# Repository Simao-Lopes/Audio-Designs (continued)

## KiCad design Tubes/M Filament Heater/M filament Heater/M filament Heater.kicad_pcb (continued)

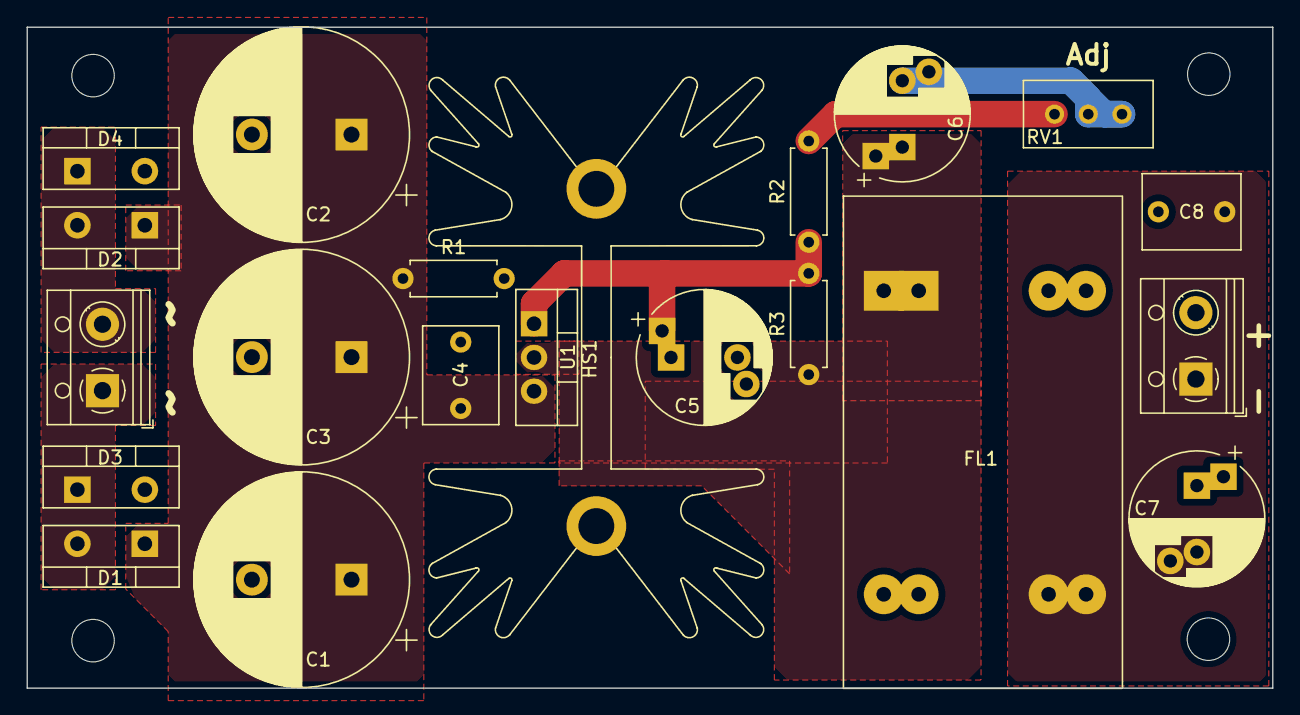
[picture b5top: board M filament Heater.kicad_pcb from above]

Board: 2 copper layers, 93.8 x 49.8 mm, 20 parts (0 on the bottom side), 9 nets.
